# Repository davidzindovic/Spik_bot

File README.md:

# OPIS
SpikBot je manipulator namenjen robotizirani endoterapiji dreves, ki obratuje s pomočjo STM32H750B-DK razvojne plošče.
Drevo zazna s pomočjo Intel RealSense D455 RGB-D kamere, ki je povezana na osebni računalnik.
Po sadovnjaku premikamo manipulator s pomočjo AWD+AWS mobilne platforme, ki jo upravlja BeckHoff PLC krmilnik.

# REPOZITORIJ

- **Hardware** - Datoteke za električno shemo in električno vezje
- **Meritve** - Datoteke namenjene uvodnim meritvah sile in traja (arhivirano)
- **PC** - Programske datoteke, ki tečejo na osebnem računalniku
- **RPI** - Programske datoteke, ki tečejo na RaspberryPi (arhivirano)
- **STM32** - Programske datoteke, ki teče na STM32

# UPORABA

Napravo lahko uporabljamo v kombinaciji z računalnikom in STM32 krmilnikom preko tipkovnice.
Za Uporabo preko igralnega ploščka moramo povezati računalnik na mobilno platformo.
Navodila za uporabo se izpišejo ob začetku programa.

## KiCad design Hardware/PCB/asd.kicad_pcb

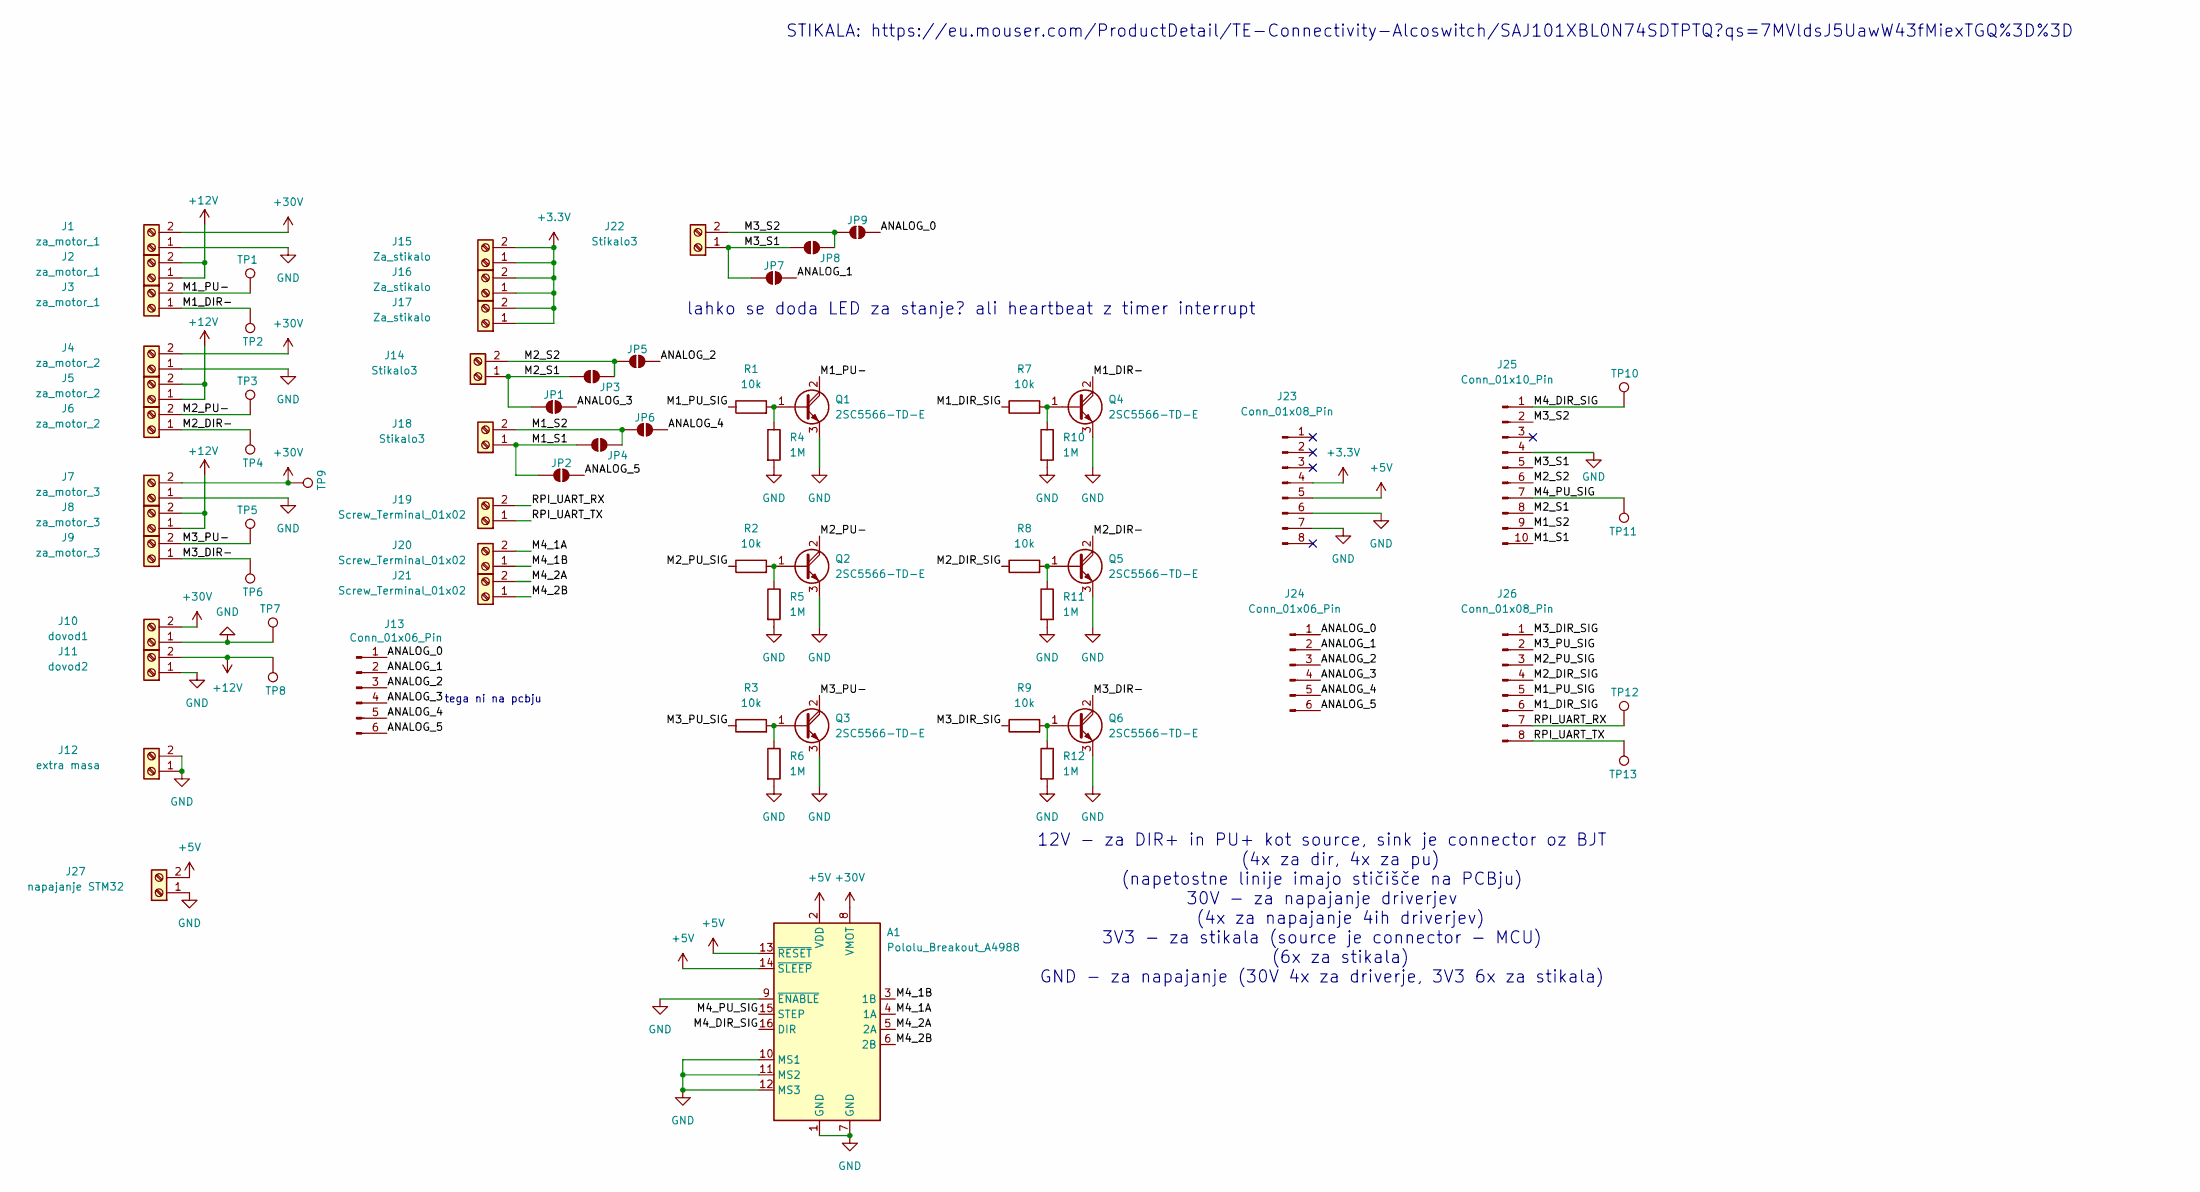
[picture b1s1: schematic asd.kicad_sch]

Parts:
A1: Pololu_Breakout_A4988; Pololu_Breakout-16_15.2x20.3mm
J1, J2, J3: za_motor_1; TerminalBlock_MetzConnect_Type073_RT02602HBLU_1x02_P5.08mm_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
J4, J5, J6: za_motor_2; TerminalBlock_MetzConnect_Type073_RT02602HBLU_1x02_P5.08mm_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
J7, J8, J9: za_motor_3; TerminalBlock_MetzConnect_Type073_RT02602HBLU_1x02_P5.08mm_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
J10: dovod1; TerminalBlock_MetzConnect_Type073_RT02602HBLU_1x02_P5.08mm_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
J11: dovod2; TerminalBlock_MetzConnect_Type073_RT02602HBLU_1x02_P5.08mm_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
J12: extra masa; TerminalBlock_MetzConnect_Type073_RT02602HBLU_1x02_P5.08mm_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
J13, J24: Conn_01x06_Pin; PinHeader_1x06_P2.54mm_Vertical
J14, J18, J22: Stikalo3; TerminalBlock_MetzConnect_Type073_RT02602HBLU_1x02_P5.08mm_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
J15, J16, J17: Za_stikalo; TerminalBlock_MetzConnect_Type073_RT02602HBLU_1x02_P5.08mm_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
J19, J20, J21: Screw_Terminal_01x02; TerminalBlock_MetzConnect_Type073_RT02602HBLU_1x02_P5.08mm_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
J23, J26: Conn_01x08_Pin; PinHeader_1x08_P2.54mm_Vertical
J25: Conn_01x10_Pin; PinHeader_1x10_P2.54mm_Vertical
J27: napajanje STM32; TerminalBlock_MetzConnect_Type073_RT02602HBLU_1x02_P5.08mm_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
JP1, JP2, JP3, JP4, JP5, JP6, JP7, JP8, JP9: SolderJumper_2_Open; SolderJumper-2_P1.3mm_Open_TrianglePad1.0x1.5mm
Q1, Q2, Q3, Q4, Q5, Q6: 2SC5566-TD-E; SOT-89-3
R1, R2, R3, R7, R8, R9: 10k; R_0805_2012Metric
R4, R5, R6, R10, R11, R12: 1M; R_0805_2012Metric
TP1, TP2, TP3, TP4, TP5, TP6, TP7, TP8, TP9, TP10, TP11, TP12, TP13: TestPoint; TestPoint_Pad_D2.5mm

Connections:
+3.3V: J15.1, J15.2, J16.1, J16.2, J17.1, J17.2, J23.4
+5V: A1.2 (VDD), A1.13 (~RESET), A1.14 (~SLEEP), J23.5, J27.2
+12V: J2.1, J2.2, J5.1, J5.2, J8.1, J8.2, J11.2, TP8.1
+30V: A1.8 (VMOT), J1.2, J4.2, J7.2, J10.2, TP9.1
/ANALOG_0: J13.1, J24.1, JP9.2 (B)
/ANALOG_1: J13.2, J24.2, JP7.2 (B)
/ANALOG_2: J13.3, J24.3, JP5.2 (B)
/ANALOG_3: J13.4, J24.4, JP1.2 (B)
/ANALOG_4: J13.5, J24.5, JP6.2 (B)
/ANALOG_5: J13.6, J24.6, JP2.2 (B)
/M1_DIR-: J3.1, Q4.2 (C), TP2.1
/M1_DIR_SIG: J26.6, R7.1
/M1_PU-: J3.2, Q1.2 (C), TP1.1
/M1_PU_SIG: J26.5, R1.1
/M1_S1: J18.1, J25.10, JP2.1 (A), JP4.1 (A)
/M1_S2: J18.2, J25.9, JP4.2 (B), JP6.1 (A)
/M2_DIR-: J6.1, Q5.2 (C), TP4.1
/M2_DIR_SIG: J26.4, R8.1
/M2_PU-: J6.2, Q2.2 (C), TP3.1
/M2_PU_SIG: J26.3, R2.1
/M2_S1: J14.1, J25.8, JP1.1 (A), JP3.1 (A)
/M2_S2: J14.2, J25.6, JP3.2 (B), JP5.1 (A)
/M3_DIR-: J9.1, Q6.2 (C), TP6.1
/M3_DIR_SIG: J26.1, R9.1
/M3_PU-: J9.2, Q3.2 (C), TP5.1
/M3_PU_SIG: J26.2, R3.1
/M3_S1: J22.1, J25.5, JP7.1 (A), JP8.1 (A)
/M3_S2: J22.2, J25.2, JP8.2 (B), JP9.1 (A)
/M4_1A: A1.4 (1A), J20.2
/M4_1B: A1.3 (1B), J20.1
/M4_2A: A1.5 (2A), J21.2
/M4_2B: A1.6 (2B), J21.1
/M4_DIR_SIG: A1.16 (DIR), J25.1, TP10.1
/M4_PU_SIG: A1.15 (STEP), J25.7, TP11.1
/RPI_UART_RX: J19.2, J26.7, TP12.1
/RPI_UART_TX: J19.1, J26.8, TP13.1
GND: A1.1 (GND), A1.7 (GND), A1.9 (~ENABLE), A1.10 (MS1), A1.11 (MS2), A1.12 (MS3), J1.1, J4.1, J7.1, J10.1, J11.1, J12.1, J12.2, J23.6, J23.7, J25.4, J27.1, Q1.3 (E), Q2.3 (E), Q3.3 (E), Q4.3 (E), Q5.3 (E), Q6.3 (E), R4.2, R5.2, R6.2, R10.2, R11.2, R12.2, TP7.1
unnamed: Q1.1 (B), R1.2, R4.1
unnamed: Q2.1 (B), R2.2, R5.1
unnamed: Q3.1 (B), R3.2, R6.1
unnamed: Q4.1 (B), R7.2, R10.1
unnamed: Q5.1 (B), R8.2, R11.1
unnamed: Q6.1 (B), R9.2, R12.1

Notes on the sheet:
tega ni na pcbju
12V - za DIR+ in PU+ kot source, sink je connector oz BJT (4x za dir, 4x za pu) (napetostne linije imajo stičišče na PCBju) 30V - za napajanje driverjev (4x za napajanje 4ih driverjev) 3V3 - za stikala (source je connector - MCU) (6x za stikala) GND - za napajanje (30V 4x za driverje, 3V3 6x za sti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
lahko se doda LED za stanje? ali heartbeat z timer interrupt
STIKALA: https://eu.mouser.com/ProductDetail/TE-Connectivity-Alcoswitch/SAJ101XBL0N74SDTPTQ?qs=7MVldsJ5UawW43fMiexTGQ%3D%3D

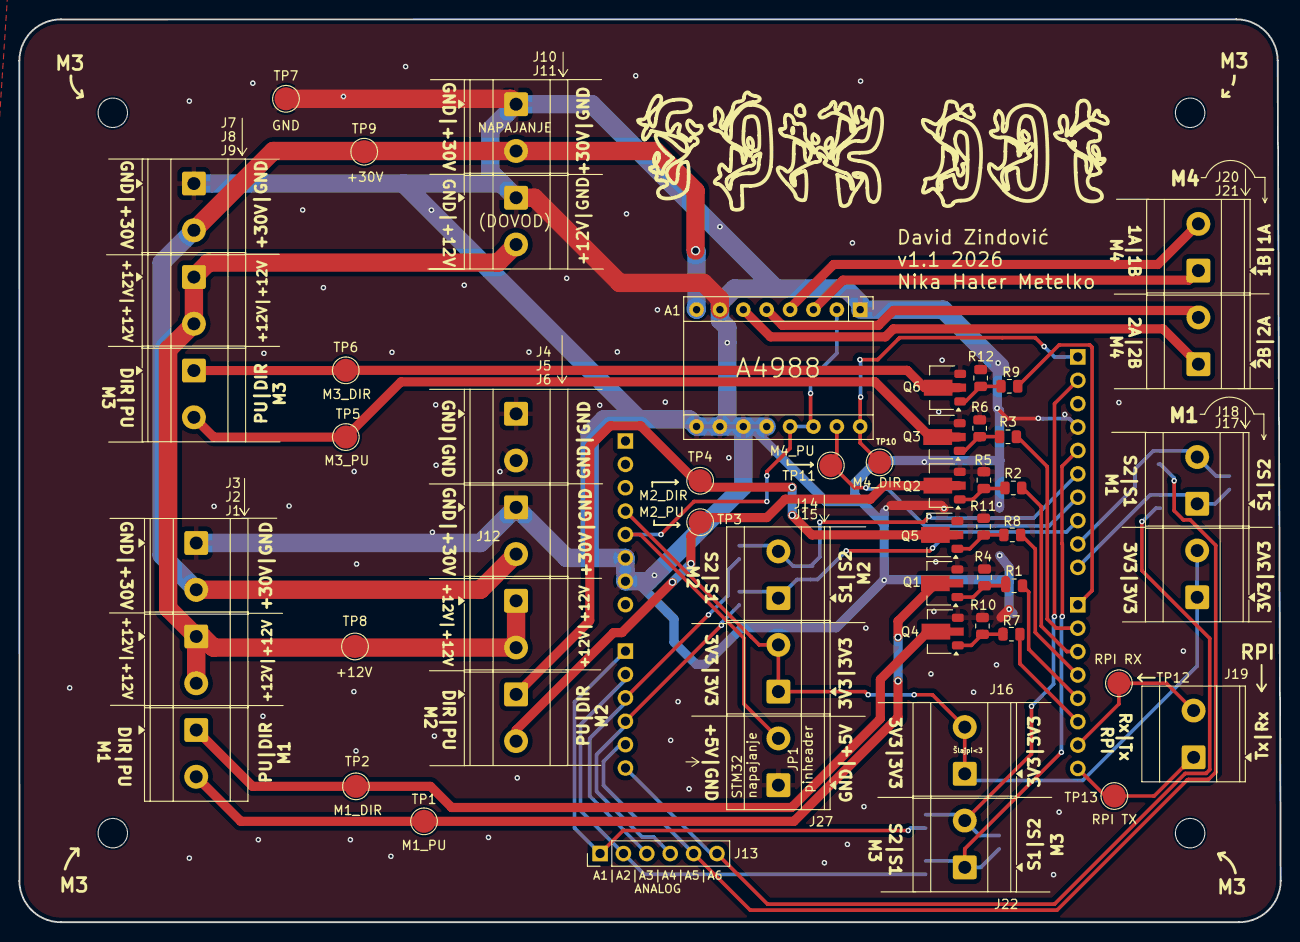
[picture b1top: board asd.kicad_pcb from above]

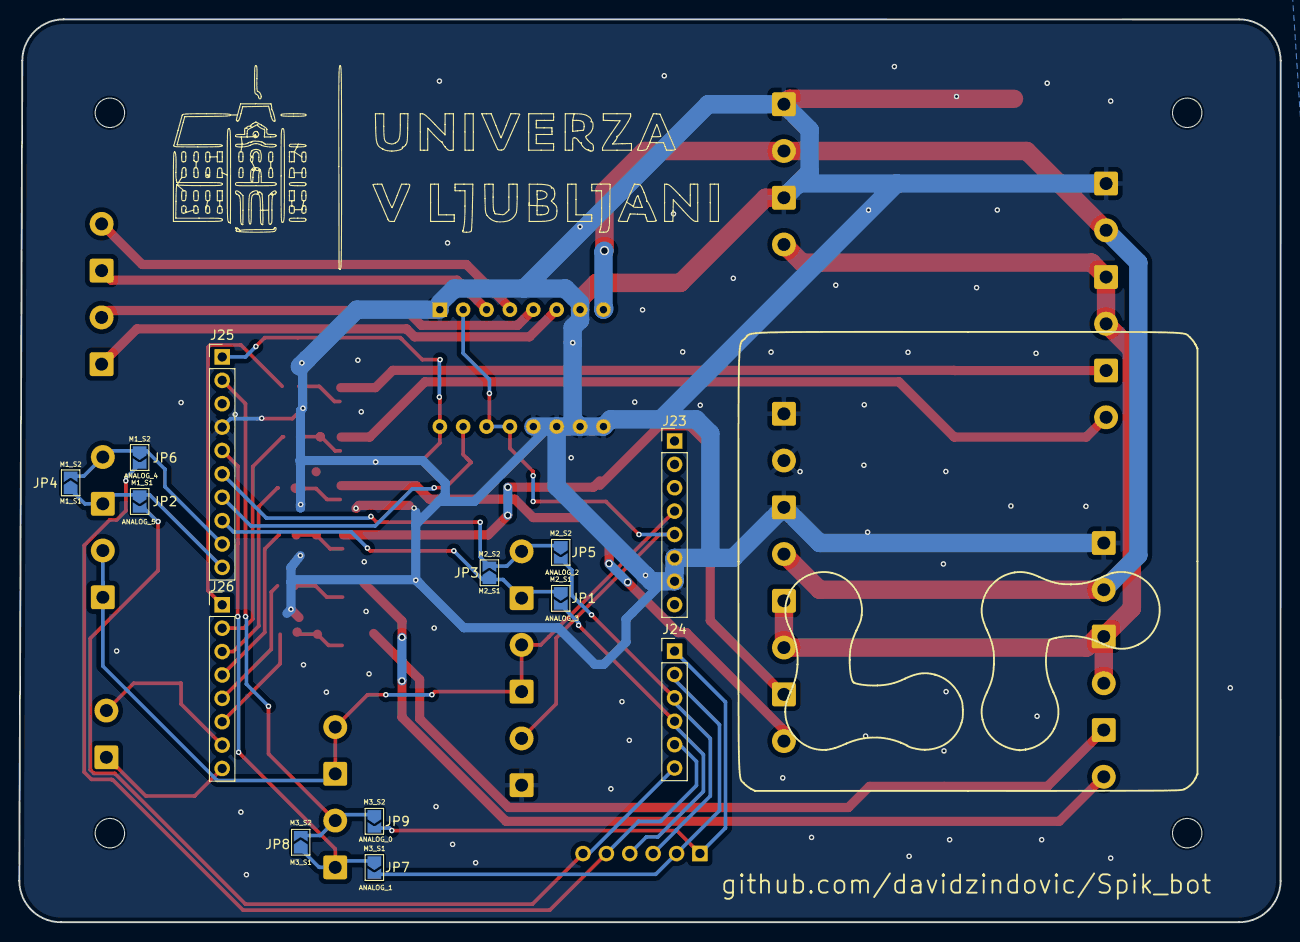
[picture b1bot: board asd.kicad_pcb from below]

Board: 2 copper layers, 137.0 x 98.1 mm, 69 parts (13 on the bottom side), 43 nets.

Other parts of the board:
REF: MountingHole_3.2mm_M3

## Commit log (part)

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2025-10-16 Modify data reception and buffer reset logic
2025-10-16 Add serial communication functions for RPI
2025-10-16 Rename RPI/u1.py to RPI/arhiv/u1.py
2025-10-16 Rename RPI/u2.py to RPI/arhiv/u2.py
2025-10-16 Rename RPI/u3.py to RPI/arhiv/u3.py
2025-10-16 Rename RPI/u4.py to RPI/arhiv/u4.py
2025-10-16 Rename RPI/uart_debug.py to RPI/arhiv/uart_debug.py
2025-10-16 Rename RPI/uart_test.py to RPI/arhiv/uart_test.py
2025-10-19 Remove unnecessary comments and clean up imports
2025-10-19 Remove unnecessary comments and whitespace
2025-10-19 Fix import statements in main.py
2025-10-19 Use global 'ser' for serial communication
    Refactor serial initialization to use global 'ser' variable.
2025-10-19 Add serial_close function to close serial connection
2025-10-19 Correct message receiving logic in spik_bot_serial.py
    Fix indentation and return statement in receiving message logic.
2025-12-13 Enhance serial communication in main.py
    Added serial transmission of coordinates and improved message logging.
2025-12-14 Update main.c
    Usart sporočila delajo, shranijo x,y koordinati iz sporočila in tudi preverita veljavnost sporočila
2025-12-15 Rename README.md to installation.md
2025-12-18 Add cylinder detection and 3D coordinate calculation
2025-12-18 Add get_spik_point_and_sketch functionality
2025-12-18 Rename get_spik_point_and_sketch to get_spik_point_and_sketch.py
2025-12-20 Rename data_capture.py to capture_and_save_images.py
2025-12-20 Rename RPI/zajeti_podatki/1barva.png to RPI/zajeti_podatki/krneki/1barva.png
2025-12-20 Rename RPI/zajeti_podatki/1globina.npy to RPI/zajeti_podatki/krneki/1globina.npy
2026-03-23 Rename README.md to PatchNotes.md
2026-05-07 Popravljeno mapiranje senzorja za tlak
2026-05-07 Rename meritve_pritisk_stm32.py to Meritve/meritve_pritisk_stm32.py
2026-05-19 Refactor motor control logic and add test cases
    Comment out unused code and add test sequences for motor control.
2026-05-19 Rename novo_sam_se_ne_dela.c to arhiv.c
2026-05-22 stabilen tof in h bridge
2026-05-22 stabilen tof in h bridge. Flag za uart dodan
